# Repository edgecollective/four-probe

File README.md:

# four-probe

# Timers

- Great examples of using the samd21 timers and interrupts: https://github.com/maxbader/arduino_tools/tree/master/libraries

- Another great example: https://github.com/nebs/arduino-zero-timer-demo/blob/master/src/main.cpp

# Circuit

- Analog Devices "Fully Automatic Self-Calibrated Conductivity Measurements": http://www.analog.com/en/analog-dialogue/articles/fully-automatic-self-calibrated-conductivity-measurement-system.html;  Reference design document: http://www.analog.com/media/en/reference-design-documentation/reference-designs/CN0359.pdf

# Misc Notes

peak detector
https://electronics.stackexchange.com/questions/57866/how-to-sample-and-hold-on-very-narrow-pulse

https://gist.github.com/jdneo/43be30d85080b175cb5aed3500d3f989

arduino zero timer interrupts:
https://forum.arduino.cc/index.php?topic=332275.0

arduino timer library!
https://github.com/avandalen/avdweb_SAMDtimer
http://www.avdweb.nl/arduino/libraries/samd21-timer.html

http://www.avdweb.nl/shop/store.html

http://asf.atmel.com/docs/latest/samr21/html/group__asfdoc__sam0__tcc__group.html#asfdoc_sam0_tcc_block_diagram

general reference for samd21:
http://ww1.microchip.com/downloads/en/DeviceDoc/40001882A.pdf

https://forum.arduino.cc/index.php?topic=332275.15
https://forum.arduino.cc/index.php?topic=454243.0 --- intro to the timer

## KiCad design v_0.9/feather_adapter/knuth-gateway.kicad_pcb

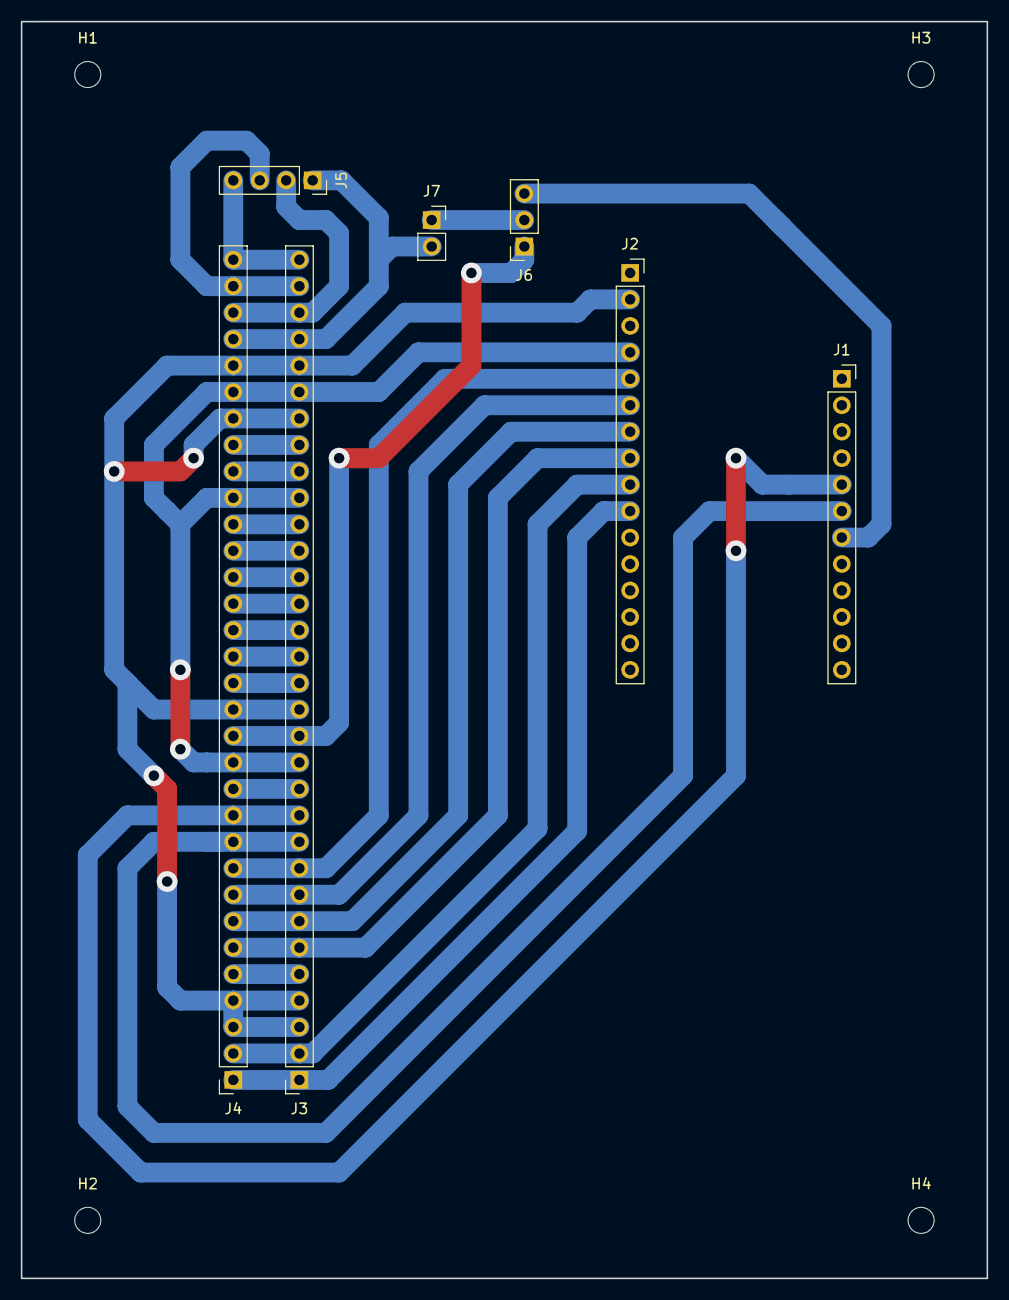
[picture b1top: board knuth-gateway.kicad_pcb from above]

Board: 2 copper layers, 92.7 x 120.7 mm, 11 parts (0 on the bottom side), 28 nets.

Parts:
H1, H2, H3, H4: MountingHole; MountingHole_2.5mm
J1: FeatherLora1; PinSocket_1x12_P2.54mm_Vertical
J2: FeatherLora2; PinSocket_1x16_P2.54mm_Vertical
J3, J4: Conn_01x32_Male; PinSocket_1x32_P2.54mm_Vertical
J5: Conn_01x04_Female; PinSocket_1x04_P2.54mm_Vertical
J6: Conn_01x03_Female; PinSocket_1x03_P2.54mm_Vertical
J7: Conn_01x02_Female; PinSocket_1x02_P2.54mm_Vertical

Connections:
+3V3: J2.2, J3.3, J3.4, J3.15, J3.26, J3.28, J4.3, J4.4, J4.15, J4.26, J4.28
A0: J2.5, J3.9, J4.9
A1: J2.6, J3.8, J4.8
A2: J2.7, J3.7, J4.7
A3: J2.8, J3.6, J4.6
A4: J2.9, J3.2, J4.2
A5: J2.10, J3.1, J4.1
D10: J1.7, J6.3
D11: J1.6, J3.10, J4.10
D12: J1.5, J3.11, J4.11
GND: J2.4, J3.13, J3.23, J3.27, J4.13, J4.23, J4.27
GNDREF: J3.14, J4.14, J6.1
unnamed: J3.5, J4.5
unnamed: J3.12, J4.12
unnamed: J3.16, J4.16
unnamed: J3.17, J4.17
unnamed: J3.18, J4.18
unnamed: J3.19, J4.19
unnamed: J3.20, J4.20
unnamed: J3.21, J4.21
unnamed: J3.22, J4.22
unnamed: J3.24, J4.24
unnamed: J3.25, J4.25
unnamed: J6.2, J7.1
PT1: J3.29, J4.29, J5.1, J7.2
PT2: J3.30, J4.30, J5.2
PT3: J3.31, J4.31, J5.3
PT4: J3.32, J4.32, J5.4

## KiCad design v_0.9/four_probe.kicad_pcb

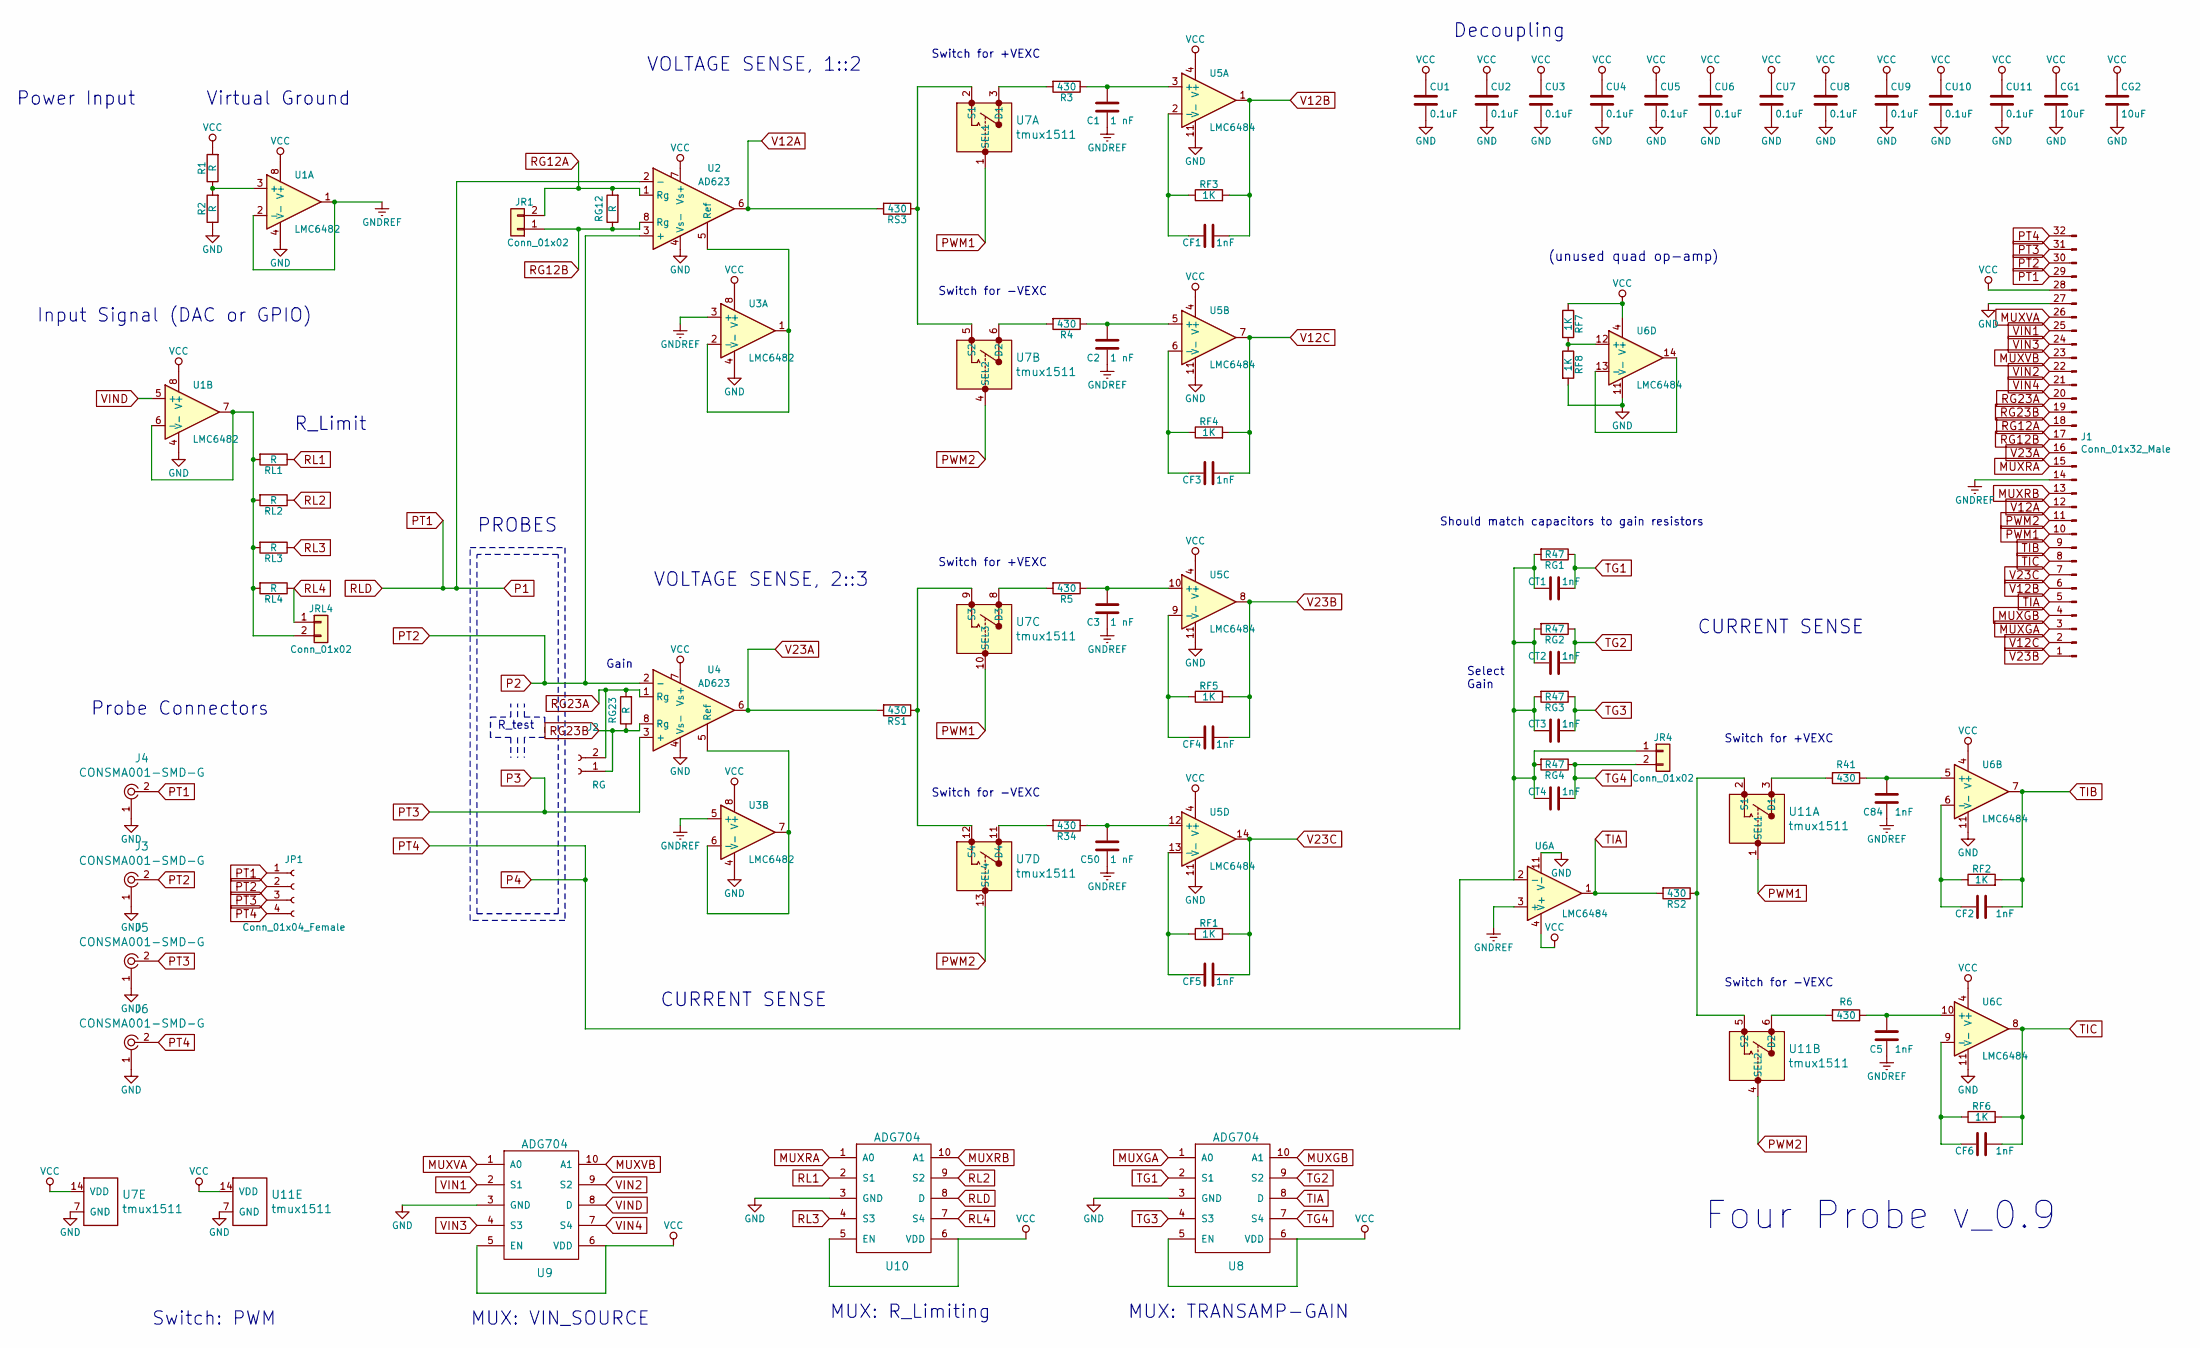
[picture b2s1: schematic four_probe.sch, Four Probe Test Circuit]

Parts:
C1, C2, C3, C50: 1 nF; C_0603_1608Metric
C5, C84: 1nF; C_0603_1608Metric
CF1, CF2, CF3, CF4, CF5, CF6: 1nF; C_0603_1608Metric
CG1, CG2: 10uF; C_0603_1608Metric
CT1, CT2, CT3, CT4: 1nF; C_0603_1608Metric
CU1, CU2, CU3, CU4, CU5, CU6, CU7, CU8, CU9, CU10, CU11: 0.1uF; C_0603_1608Metric
J1: Conn_01x32_Male; PinHeader_1x32_P2.54mm_Vertical
J2: RG; PinSocket_1x02_P2.54mm_Vertical
J3, J4, J5, J6: CONSMA001-SMD-G; RF_SMA_Receptical_Vertical_CONSMA001-SMD-G; MPN CONSMA001-SMD-G; Digi-Key_PN CONSMA001-SMD-G-ND
JP1: Conn_01x04_Female; PinSocket_1x04_P2.54mm_Vertical
JR1, JR4: Conn_01x02; PinSocket_1x02_P2.54mm_Vertical
JRL4: Conn_01x02; PinSocket_1x02_P2.54mm_Vertical
R1, R2: R; R_0603_1608Metric
R3, R4, R5, R6, R34, R41: 430; R_0603_1608Metric
RF1, RF2, RF3, RF4, RF5, RF6, RF7, RF8: 1K; R_0603_1608Metric
RG1, RG2, RG3, RG4: R47; R_0603_1608Metric
RG12, RG23: R; R_0603_1608Metric
RL1, RL2, RL3, RL4: R; R_0603_1608Metric
RS1, RS2, RS3: 430; R_0603_1608Metric
U1, U3: LMC6482; SOIC-8_3.9x4.9mm_P1.27mm
U2, U4: AD623; SOIC-8_3.9x4.9mm_P1.27mm
U5, U6: LMC6484; SOIC-14_3.9x8.7mm_P1.27mm
U7, U11: tmux1511; TSSOP-14_W4.4mm
U8, U9, U10: ADG704; MSOP-10_3x3mm_P0.5mm

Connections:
GND: CG1.2, CG2.2, CU1.2, CU2.2, CU3.2, CU4.2, CU5.2, CU6.2, CU7.2, CU8.2, CU9.2, CU10.2, CU11.2, J1.27, J3.1, J4.1, J5.1, J6.1, R2.1, RF8.2, U1.4 (V-), U2.4 (Vs-), U3.4 (V-), U4.4 (Vs-), U5.11 (V-), U6.11 (V-), U7.7 (GND), U8.3 (GND), U9.3 (GND), U10.3 (GND), U11.7 (GND)
GNDREF: C1.1, C2.1, C3.1, C5.1, C50.1, C84.1, J1.14, U1.1, U1.2 (-), U3.3 (+), U3.5 (+), U6.3 (+)
MUXGA: J1.3, U8.1 (A0)
MUXGB: J1.4, U8.10 (A1)
MUXRA: J1.15, U10.1 (A0)
MUXRB: J1.13, U10.10 (A1)
MUXVA: J1.26, U9.1 (A0)
MUXVB: J1.23, U9.10 (A1)
unnamed: C1.2, R3.1, U5.3 (+)
unnamed: C2.2, R4.1, U5.5 (+)
unnamed: C3.2, R5.1, U5.10 (+)
unnamed: C5.2, R6.1, U6.10 (+)
unnamed: C50.2, R34.1, U5.12 (+)
unnamed: C84.2, R41.1, U6.5 (+)
unnamed: CF1.2, RF3.1, U5.2 (-)
unnamed: CF2.2, RF2.1, U6.6 (-)
unnamed: CF3.2, RF4.1, U5.6 (-)
unnamed: CF4.2, RF5.1, U5.9 (-)
unnamed: CF5.2, RF1.1, U5.13 (-)
unnamed: CF6.2, RF6.1, U6.9 (-)
unnamed: JRL4.2, RL1.2, RL2.2, RL3.2, RL4.2, U1.6 (-), U1.7
unnamed: R1.1, R2.2, U1.3 (+)
unnamed: R3.2, U7.3 (D1)
unnamed: R4.2, U7.6 (D2)
unnamed: R5.2, U7.8 (D3)
unnamed: R6.2, U11.6 (D2)
unnamed: R34.2, U7.11 (D4)
unnamed: R41.2, U11.3 (D1)
unnamed: RF7.2, RF8.1, U6.12 (+)
unnamed: RS1.1, U7.9 (S3), U7.12 (S4)
unnamed: RS2.1, U11.2 (S1), U11.5 (S2)
unnamed: RS3.1, U7.2 (S1), U7.5 (S2)
unnamed: U2.5 (Ref), U3.1, U3.2 (-)
unnamed: U3.6 (-), U3.7, U4.5 (Ref)
unnamed: U6.13 (-), U6.14
P1: J1.29, J4.2, JP1.1, U2.2 (-), U10.8 (D)
P2: J1.30, J3.2, JP1.2, U2.3 (+), U4.2 (-)
P3: J1.31, J5.2, JP1.3, U4.3 (+)
P4: CT1.2, CT2.2, CT3.2, CT4.2, J1.32, J6.2, JP1.4, JR4.1, RG1.2, RG2.2, RG3.2, RG4.2, U6.2 (-)
PWM1: J1.10, U7.1 (SEL1), U7.10 (SEL3), U11.1 (SEL1)
PWM2: J1.11, U7.4 (SEL2), U7.13 (SEL4), U11.4 (SEL2)
RG12A: J1.18, JR1.2, RG12.2, U2.1 (Rg)
RG12B: J1.17, JR1.1, RG12.1, U2.8 (Rg)
RG23A: J1.20, J2.2, RG23.2, U4.1 (Rg)
RG23B: J1.19, J2.1, RG23.1, U4.8 (Rg)
RL1: RL1.1, U10.2 (S1)
RL2: RL2.1, U10.9 (S2)
RL3: RL3.1, U10.4 (S3)
RL4: JRL4.1, RL4.1, U10.7 (S4)
TG1: CT1.1, RG1.1, U8.2 (S1)
TG2: CT2.1, RG2.1, U8.9 (S2)
TG3: CT3.1, RG3.1, U8.4 (S3)
TG4: CT4.1, JR4.2, RG4.1, U8.7 (S4)
TIA: J1.5, RS2.2, U6.1, U8.8 (D)
TIB: CF2.1, J1.9, RF2.2, U6.7
TIC: CF6.1, J1.8, RF6.2, U6.8
V12A: J1.12, RS3.2, U2.6
V12B: CF1.1, J1.6, RF3.2, U5.1
V12C: CF3.1, J1.2, RF4.2, U5.7
V23A: J1.16, RS1.2, U4.6
V23B: CF4.1, J1.1, RF5.2, U5.8
V23C: CF5.1, J1.7, RF1.2, U5.14
VCC: CG1.1, CG2.1, CU1.1, CU2.1, CU3.1, CU4.1, CU5.1, CU6.1, CU7.1, CU8.1, CU9.1, CU10.1, CU11.1, J1.28, R1.2, RF7.1, U1.8 (V+), U2.7 (Vs+), U3.8 (V+), U4.7 (Vs+), U5.4 (V+), U6.4 (V+), U7.14 (VDD), U8.5 (EN), U8.6 (VDD), U9.5 (EN), U9.6 (VDD), U10.5 (EN), U10.6 (VDD), U11.14 (VDD)
VIN1: J1.25, U9.2 (S1)
VIN2: J1.22, U9.9 (S2)
VIN3: J1.24, U9.4 (S3)
VIN4: J1.21, U9.7 (S4)
VIND: U1.5 (+), U9.8 (D)

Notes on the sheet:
Input Signal (DAC or GPIO)
R_test
Gain
Switch for +VEXC
Switch for -VEXC
Select Gain
MUX: R_Limiting
Switch: PWM
MUX: VIN_SOURCE
MUX: TRANSAMP-GAIN
CURRENT SENSE
VOLTAGE SENSE, 1::2
VOLTAGE SENSE, 2::3
PROBES
Four Probe v_0.9
Virtual Ground
R_Limit
Power Input
Decoupling
(unused quad op-amp)
Should match capacitors to gain resistors
Probe Connectors

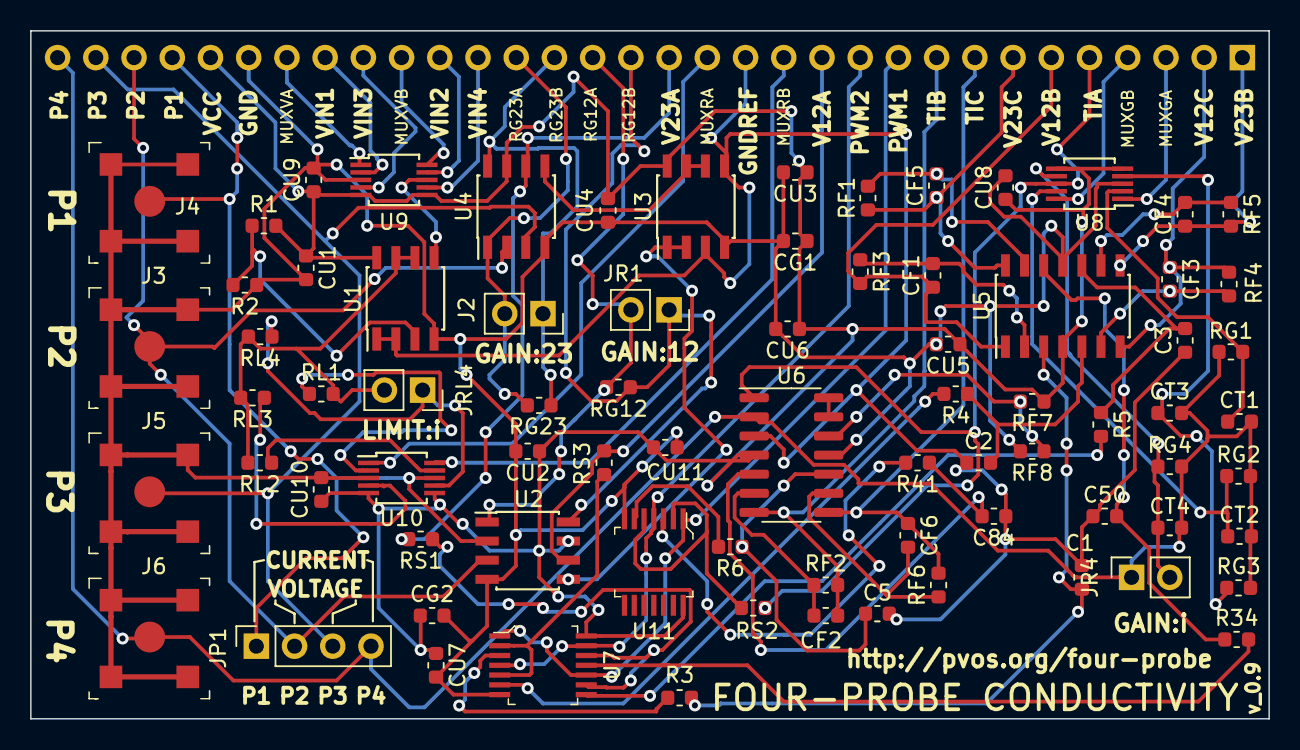
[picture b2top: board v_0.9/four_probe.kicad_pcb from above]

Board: 2 copper layers, 82.3 x 45.7 mm, 79 parts (1 on the bottom side), 68 nets.

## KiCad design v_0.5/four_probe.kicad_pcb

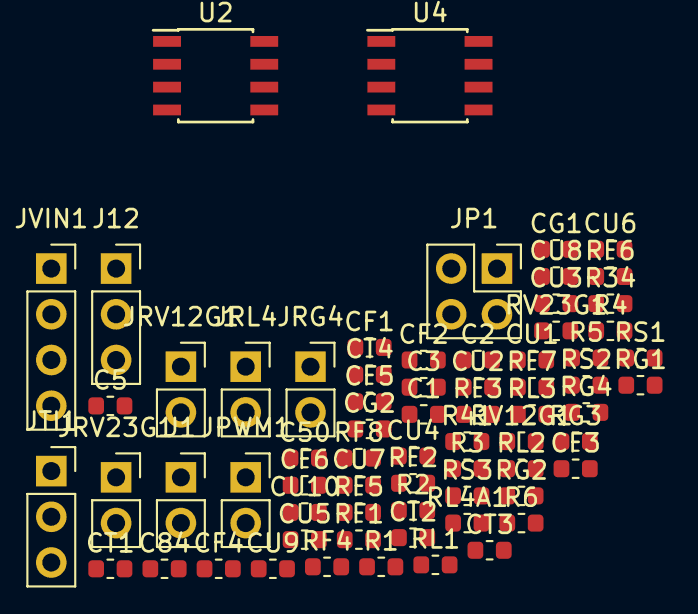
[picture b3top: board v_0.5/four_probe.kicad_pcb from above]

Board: 2 copper layers, 69 parts (0 on the bottom side), 42 nets, no tracks yet.

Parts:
C1, C2, C3, C50: 1 nF; C_0603_1608Metric
C5, C84: 1nF; C_0603_1608Metric
CF1, CF2, CF3, CF4, CF5, CF6: 1nF; C_0603_1608Metric
CG1, CG2: 10uF; C_0603_1608Metric
CT1, CT2, CT3, CT4: 1nF; C_0603_1608Metric
CU1, CU2, CU3, CU4, CU5, CU6, CU7, CU8, CU9, CU10: 0.1uF; C_0603_1608Metric
J1: Power_input; PinSocket_1x02_P2.54mm_Vertical
J12: Conn_01x03_Female; PinSocket_1x03_P2.54mm_Vertical
JP1: Conn_01x04_Female; PinSocket_2x02_P2.54mm_Vertical
JPWM1: Conn_01x02_Female; PinSocket_1x02_P2.54mm_Vertical
JRG4: Conn_01x02; PinSocket_1x02_P2.54mm_Vertical
JRL4: Conn_01x02; PinSocket_1x02_P2.54mm_Vertical
JRV12G1, JRV23G1: Conn_01x02; PinSocket_1x02_P2.54mm_Vertical
JTI1: Conn_01x03_Female; PinSocket_1x03_P2.54mm_Vertical
JVIN1: Conn_01x04_Female; PinSocket_1x04_P2.54mm_Vertical
R1, R2: R; R_0603_1608Metric
R3, R4, R5, R6, R34, R41: 430; R_0603_1608Metric
RF1, RF2, RF3, RF4, RF5, RF6, RF7, RF8: 1K; R_0603_1608Metric
RG1, RG2, RG3, RG4: R47; R_0603_1608Metric
RL1, RL2, RL3, RL4A1: R; R_0603_1608Metric
RS1, RS2, RS3: 430; R_0603_1608Metric
RV12G1, RV23G1: R; R_0603_1608Metric
U2, U4: AD623; SOIC-8_3.9x4.9mm_P1.27mm

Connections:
GND: CG1.2, CG2.2, CU1.2, CU2.2, CU3.2, CU4.2, CU5.2, CU6.2, CU7.2, CU8.2, CU9.2, CU10.2, J1.2, R2.1, RF8.2, U2.4, U4.4
GNDREF: C1.1, C2.1, C3.1, C5.1, C50.1, C84.1
unnamed: C1.2, R3.1
unnamed: C2.2, R4.1
unnamed: C3.2, R5.1
unnamed: C5.2, R6.1
unnamed: C50.2, R34.1
unnamed: C84.2, R41.1
unnamed: CF1.2, RF3.1
unnamed: CF2.2, RF2.1
unnamed: CF3.2, RF4.1
unnamed: CF4.2, RF5.1
unnamed: CF5.2, RF1.1
unnamed: CF6.2, RF6.1
unnamed: JRL4.2, RL1.2, RL2.2, RL3.2, RL4A1.2
unnamed: JRV12G1.1, RV12G1.1, U2.8
unnamed: JRV12G1.2, RV12G1.2, U2.1
unnamed: JRV23G1.1, RV23G1.1, U4.8
unnamed: JRV23G1.2, RV23G1.2, U4.1
unnamed: R1.1, R2.2
unnamed: RF7.2, RF8.1
P1: JP1.1, U2.2
P3: JP1.2, JP1.3, U2.3, U4.2, U4.3
P4: CT1.2, CT2.2, CT3.2, CT4.2, JP1.4, JRG4.1, RG1.2, RG2.2, RG3.2, RG4.2
PWM1-D: R3.2, R5.2, R41.2
PWM2-D: R4.2, R6.2, R34.2
RL4: JRL4.1, RL4A1.1
TG1: CT1.1, RG1.1
TG2: CT2.1, RG2.1
TG3: CT3.1, RG3.1
TG4: CT4.1, JRG4.2, RG4.1
TIA: JTI1.1, RS2.2
TIB: CF2.1, JTI1.2, RF2.2
TIC: CF6.1, JTI1.3, RF6.2
V12A: J12.1, RS3.2, U2.6
V12B: CF1.1, J12.2, RF3.2
V12C: CF3.1, J12.3, RF4.2
V23A: RS1.2, U4.6
V23B: CF4.1, RF5.2
V23C: CF5.1, RF1.2
VCC: CG1.1, CG2.1, CU1.1, CU2.1, CU3.1, CU4.1, CU5.1, CU6.1, CU7.1, CU8.1, CU9.1, CU10.1, J1.1, R1.2, RF7.1, U2.7, U4.7
VIN3: JVIN1.3, JVIN1.4

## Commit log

2019-12-29 update ;
